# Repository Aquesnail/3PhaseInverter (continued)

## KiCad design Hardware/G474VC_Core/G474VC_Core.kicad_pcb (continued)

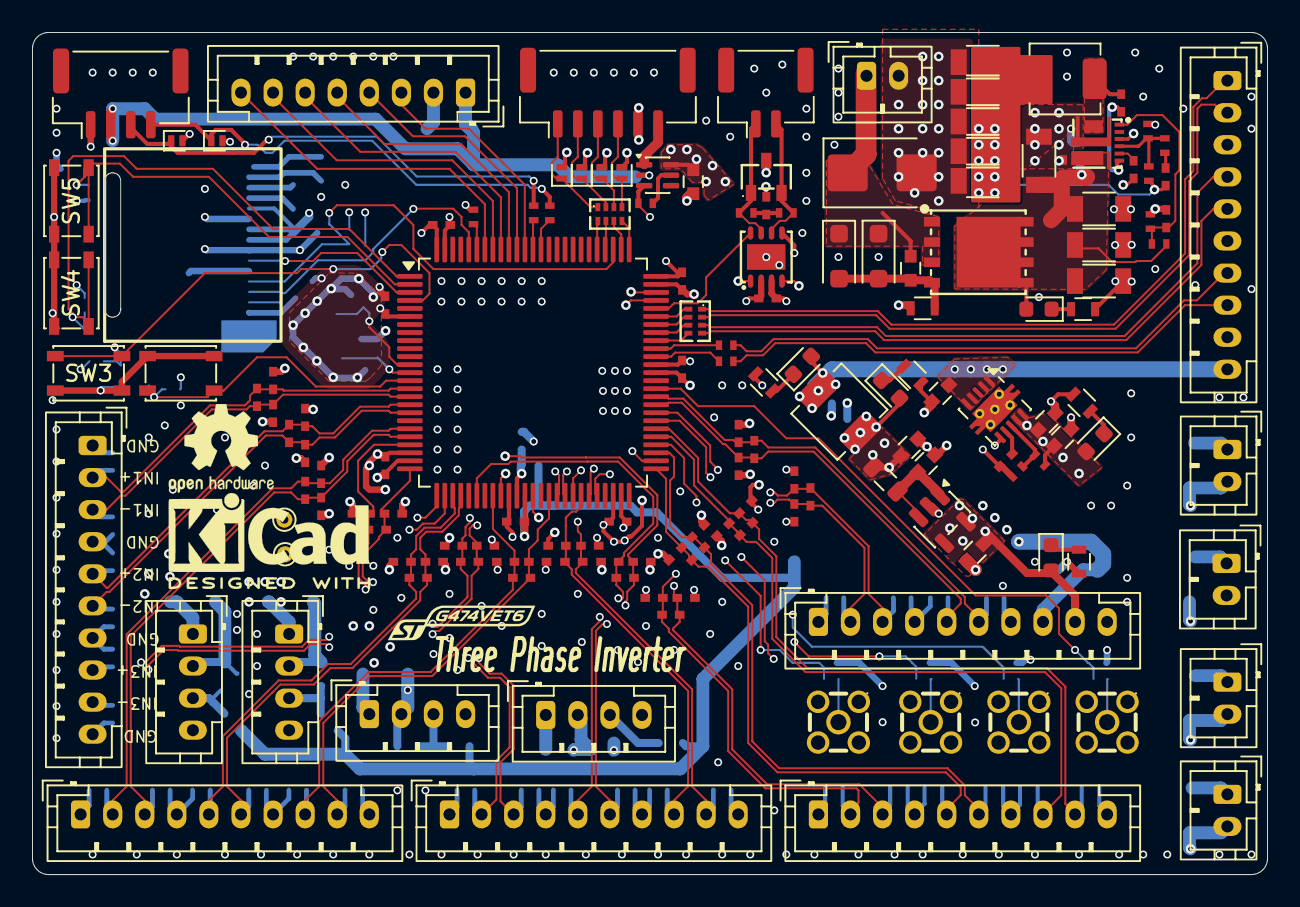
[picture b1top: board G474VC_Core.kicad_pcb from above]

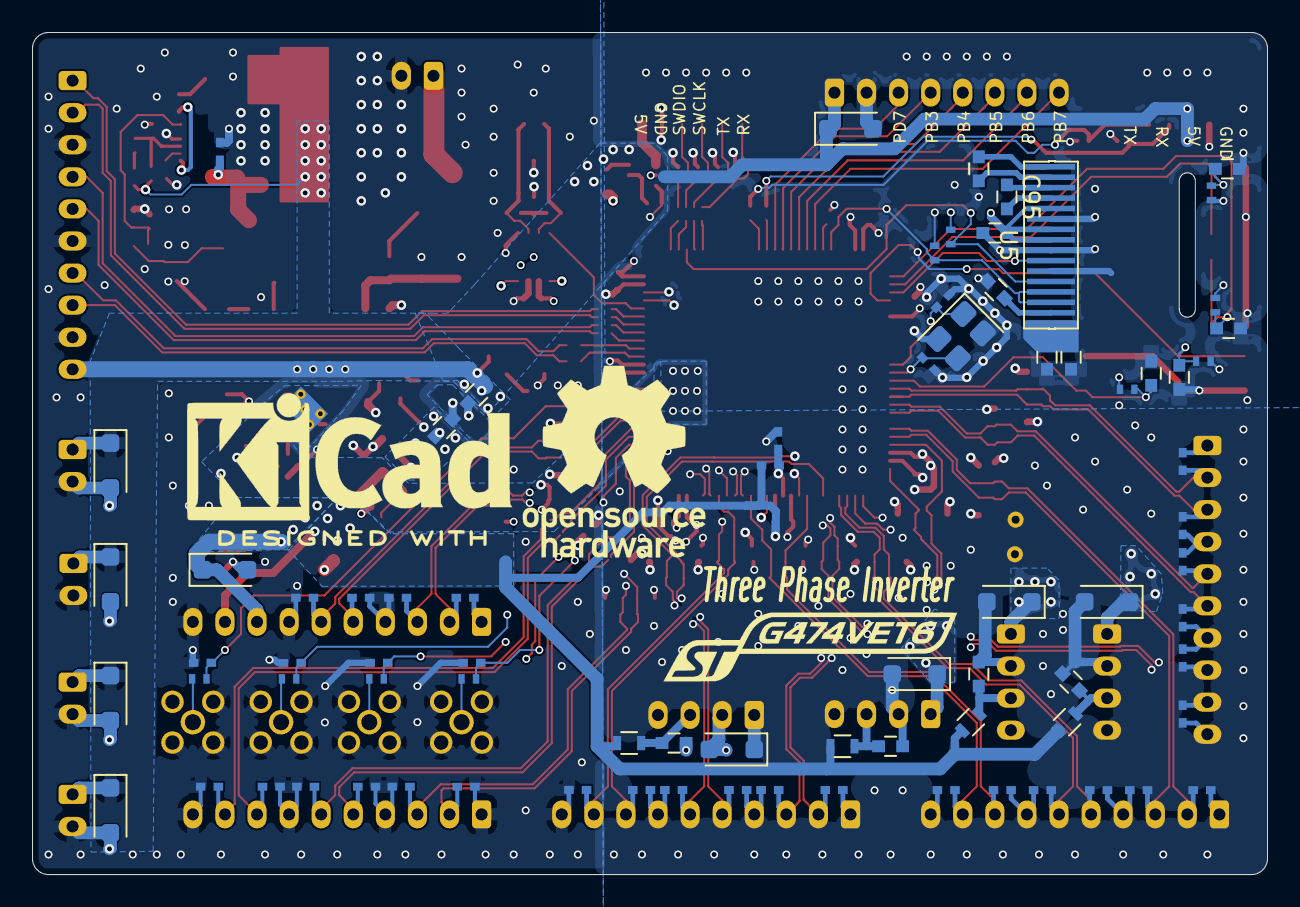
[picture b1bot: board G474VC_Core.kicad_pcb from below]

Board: 4 copper layers, 77.0 x 52.5 mm, 230 parts (79 on the bottom side), 119 nets.

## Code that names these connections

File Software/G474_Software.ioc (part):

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Mcu.Name=STM32G474V(B-C-E)Tx
Mcu.Package=LQFP100
Mcu.UserName=STM32G474VCTx
PA0.Mode=IN1-Differential
PA0.Signal=ADC1_IN1
PA1.Mode=IN1-Differential
PA1.Signal=ADC1_IN2
PA10.Signal=GPIO_Output
PA11.Mode=FDCAN_Activate
PA11.Signal=FDCAN1_RX
PA12.Mode=FDCAN_Activate
PA12.Signal=FDCAN1_TX
PA13.Mode=Serial_Wire
PA13.Signal=SYS_JTMS-SWDIO
PA14.Mode=Serial_Wire
PA14.Signal=SYS_JTCK-SWCLK
PA15.Mode=I2C
PA15.Signal=I2C1_SCL
PA2.Mode=IN3-Differential
PA2.Signal=ADC1_IN3
PA3.Mode=IN3-Differential
PA3.Signal=ADC1_IN4
PA4.Signal=COMP_DAC11_group
PA5.Signal=COMP_DAC12_group
PA6.Mode=IN3-Differential
PA6.Signal=ADC2_IN3
PA7.Mode=IN3-Differential
PA7.Signal=ADC2_IN4
PA8.Mode=Output_TA1TA2
PA8.Signal=HRTIM1_CHA1
PA9.Mode=Output_TA1TA2
PA9.Signal=HRTIM1_CHA2
PB1.Mode=IN1-Differential
PB1.Signal=ADC3_IN1
PB12.Mode=IN3-Differential
PB12.Signal=ADC4_IN3
PB14.Mode=IN3-Differential
PB14.Signal=ADC4_IN4
PB2.Mode=IN11-Differential
PB2.Signal=ADC2_IN12
PB3.Signal=GPIO_Output
PB4.Signal=GPIO_Output
PB5.Signal=GPIO_Output
PB6.Signal=GPIO_Output
PB7.Signal=GPIO_Output
PB9.Mode=I2C
PB9.Signal=I2C1_SDA
PC0.Mode=IN6-Differential
PC0.Signal=ADC1_IN6
PC1.Mode=IN6-Differential
PC1.Signal=ADC1_IN7
PC10.Mode=Asynchronous
PC10.Signal=USART3_TX
PC11.Mode=Asynchronous
PC11.Signal=USART3_RX
PC2.Mode=IN8-Differential
PC2.Signal=ADC2_IN8
PC3.Mode=IN8-Differential
PC3.Signal=ADC2_IN9
PC5.Mode=IN11-Differential
PC5.Signal=ADC2_IN11
PC6.Mode=Output_TF1TF2
PC6.Signal=HRTIM1_CHF1
PC7.Mode=Output_TF1TF2
PC7.Signal=HRTIM1_CHF2
PC8.Mode=Output_TE1TE2
PC8.Signal=HRTIM1_CHE1
PC9.Mode=Output_TE1TE2
PC9.Signal=HRTIM1_CHE2
PD1.Signal=GPIO_Input
PD10.Mode=IN7-Differential
PD10.Signal=ADC4_IN7
PD11.Mode=IN7-Differential
PD11.Signal=ADC4_IN8
PD12.Mode=IN9-Differential
PD12.Signal=ADC5_IN9
PD13.Mode=IN9-Differential
PD13.Signal=ADC5_IN10
PD2.Signal=GPIO_Input
PD3.Signal=S_TIM2_CH1
PD4.Signal=S_TIM2_CH2
PD5.Mode=Asynchronous
PD5.Signal=USART2_TX
PD6.Mode=Asynchronous
PD6.Signal=USART2_RX
PD7.Signal=GPIO_Output
PD8.Mode=IN12-Differential
PD8.Signal=ADC5_IN12
PD9.Mode=IN12-Differential
PD9.Signal=ADC5_IN13
PE0.Signal=GPIO_Output
PE1.Signal=GPIO_Output
PE10.Mode=IN14-Differential
PE10.Signal=ADC3_IN14
PE11.Mode=IN14-Differential
PE11.Signal=ADC3_IN15
PE12.Mode=IN16-Single-Ended
PE12.Signal=ADC5_IN16
PE13.Mode=IN3-Differential
PE13.Signal=ADC3_IN3
PE14.Mode=IN1-Differential
PE14.Signal=ADC4_IN1
PE15.Mode=IN1-Differential
PE15.Signal=ADC4_IN2
PE2.Signal=GPIO_Output
PE3.Signal=GPIO_Output
PE4.Signal=GPIO_Output
PE5.Signal=GPIO_Output
PE7.Mode=IN3-Differential
PE7.Signal=ADC3_IN4
PE9.Mode=IN1-Differential
PE9.Signal=ADC3_IN2
PF0-OSC_IN.Mode=HSE-External-Oscillator
PF0-OSC_IN.Signal=RCC_OSC_IN
PF1-OSC_OUT.Mode=HSE-External-Oscillator
PF1-OSC_OUT.Signal=RCC_OSC_OUT
RCC.HSE_VALUE=24000000
RCC.SYSCLKFreq_VALUE=170000000
RCC.SYSCLKSource=RCC_SYSCLKSOURCE_PLLCLK
board=custom

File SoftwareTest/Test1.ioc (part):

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Mcu.Name=STM32G474C(B-C-E)Tx
Mcu.Package=LQFP48
Mcu.UserName=STM32G474CBTx
PA0.Mode=IN1-Differential
PA0.Signal=ADC2_IN1
PA1.Mode=IN1-Differential
PA1.Signal=ADC2_IN2
PA10.Mode=Asynchronous
PA10.Signal=USART1_RX
PA13.Mode=JTAG_4_pins
PA13.Signal=SYS_JTMS-SWDIO
PA14.Mode=JTAG_4_pins
PA14.Signal=SYS_JTCK-SWCLK
PA15.Mode=JTAG_4_pins
PA15.Signal=SYS_JTDI
PA2.Mode=IN3-Differential
PA2.Signal=ADC1_IN3
PA3.Mode=IN3-Differential
PA3.Signal=ADC1_IN4
PA4.Signal=GPIO_Output
PA5.Signal=GPIO_Output
PA6.Signal=GPIO_Output
PA7.Signal=GPIO_Output
PA8.GPIOParameters=GPIO_Speed,PinState
PA8.GPIO_Speed=GPIO_SPEED_FREQ_MEDIUM
PA8.PinState=GPIO_PIN_RESET
PA8.Signal=GPIO_Output
PA9.Mode=Asynchronous
PA9.Signal=USART1_TX
PB12.Mode=Output_TC1TC2
PB12.Signal=HRTIM1_CHC1
PB13.Mode=Output_TC1TC2
PB13.Signal=HRTIM1_CHC2
PB14.Mode=IN4-Differential
PB14.Signal=ADC4_IN4
PB15.Mode=IN4-Differential
PB15.Signal=ADC4_IN5
PB3.Mode=JTAG_4_pins
PB3.Signal=SYS_JTDO-SWO
PB4.Signal=S_TIM3_CH1
PF0-OSC_IN.Mode=HSE-External-Oscillator
PF0-OSC_IN.Signal=RCC_OSC_IN
PF1-OSC_OUT.Mode=HSE-External-Oscillator
PF1-OSC_OUT.Signal=RCC_OSC_OUT
RCC.HSE_VALUE=12000000
RCC.SYSCLKFreq_VALUE=170000000
RCC.SYSCLKSource=RCC_SYSCLKSOURCE_PLLCLK
board=custom
